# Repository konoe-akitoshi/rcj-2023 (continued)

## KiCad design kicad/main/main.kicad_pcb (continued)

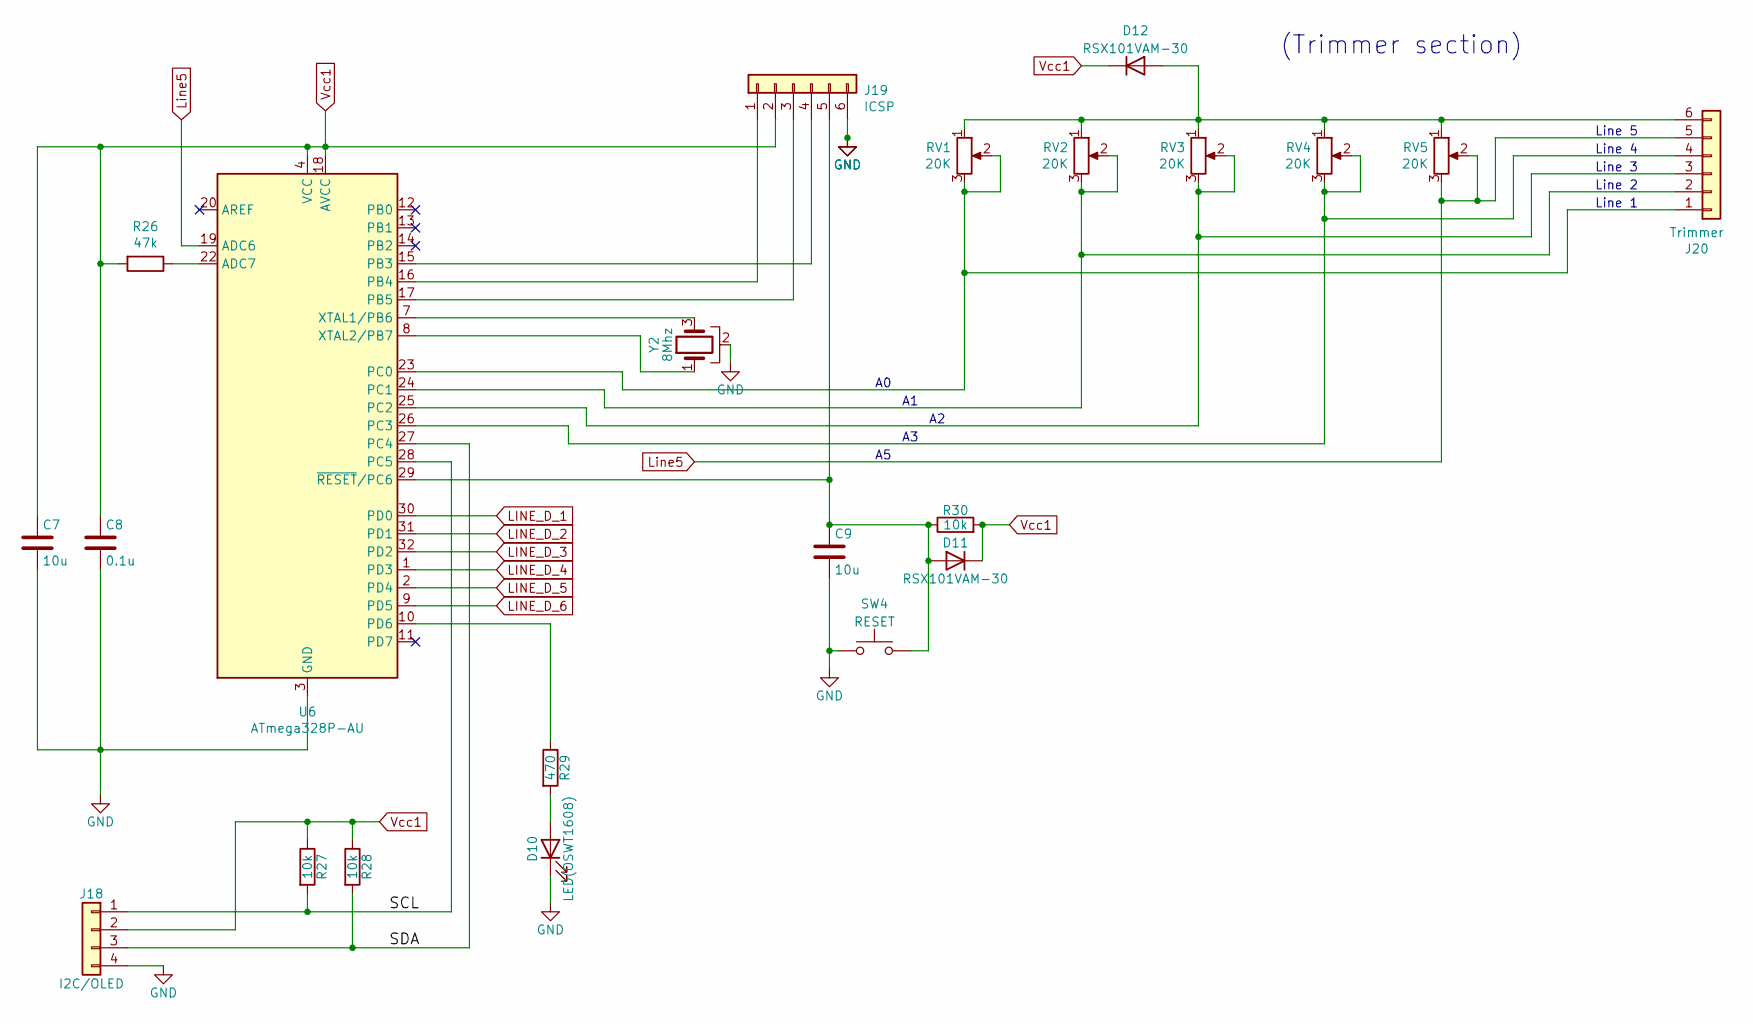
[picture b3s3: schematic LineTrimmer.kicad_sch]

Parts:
C7, C9: 10u; C_0603_1608Metric_Pad1.08x0.95mm_HandSolder
C8: 0.1u; C_0603_1608Metric_Pad1.08x0.95mm_HandSolder
D10: LED(OSWT1608); LED_SMLE13WBC8W1
D11, D12: RSX101VAM-30; D_0805_2012Metric_Pad1.15x1.40mm_HandSolder
J18: I2C/OLED; JSTB4B-ZR
J19: ICSP; JSTB6B-ZR
J20: Trimmer; JSTB6B-ZR
R26: 47k; R_0603_1608Metric_Pad0.98x0.95mm_HandSolder
R27, R28, R30: 10k; R_0603_1608Metric_Pad0.98x0.95mm_HandSolder
R29: 470; R_0603_1608Metric_Pad0.98x0.95mm_HandSolder
RV1, RV2, RV3, RV4, RV5: 20K; Trim-GF063P
SW4: RESET; THAU13-AB-R
U6: ATmega328P-AU; TQFP-32_7x7mm_P0.8mm
Y2: 8Mhz; Resonator-3Pin_W6.0mm_H3.0mm

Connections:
/LineTrimmer/SCL: J18.1, R27.2, U6.28 (PC5)
/LineTrimmer/SDA: J18.3, R28.2, U6.27 (PC4)
LINE_D_1: U6.30 (PD0); also elsewhere on the board
LINE_D_2: U6.31 (PD1); also elsewhere on the board
LINE_D_3: U6.32 (PD2); also elsewhere on the board
LINE_D_4: U6.1 (PD3); also elsewhere on the board
LINE_D_5: U6.2 (PD4); also elsewhere on the board
LINE_D_6: U6.9 (PD5); also elsewhere on the board
Line5: J20.5, RV5.2, RV5.3, U6.19 (ADC6)
unnamed: C9.1, D11.2 (A), J19.5, R30.1, SW4.2, U6.29 (~RESET/PC6)
unnamed: D10.2 (A), R29.2
unnamed: D12.2 (A), J20.6, RV1.1, RV2.1, RV3.1, RV4.1, RV5.1
unnamed: J19.1, U6.16 (PB4)
unnamed: J19.3, U6.17 (PB5)
unnamed: J19.4, U6.15 (PB3)
unnamed: J20.1, RV1.2, RV1.3, U6.23 (PC0)
unnamed: J20.2, RV2.2, RV2.3, U6.24 (PC1)
unnamed: J20.3, RV3.2, RV3.3, U6.25 (PC2)
unnamed: J20.4, RV4.2, RV4.3, U6.26 (PC3)
unnamed: R26.1, U6.22 (ADC7)
unnamed: R29.1, U6.10 (PD6)
unnamed: U6.7 (XTAL1/PB6), Y2.3
unnamed: U6.8 (XTAL2/PB7), Y2.1
SW1_6: C7.2, C8.2, C9.2, D10.1 (K), J18.4, J19.6, SW4.1, U6.3 (GND), U6.5 (GND), U6.21 (GND), Y2.2; also elsewhere on the board
Vcc1: C7.1, C8.1, D11.1 (K), D12.1 (K), J18.2, J19.2, R26.2, R27.1, R28.1, R30.2, U6.4 (VCC), U6.6 (VCC), U6.18 (AVCC)

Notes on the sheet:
Line 1
Line 2
Line 3
(Trimmer section)
Line 4
Line 5

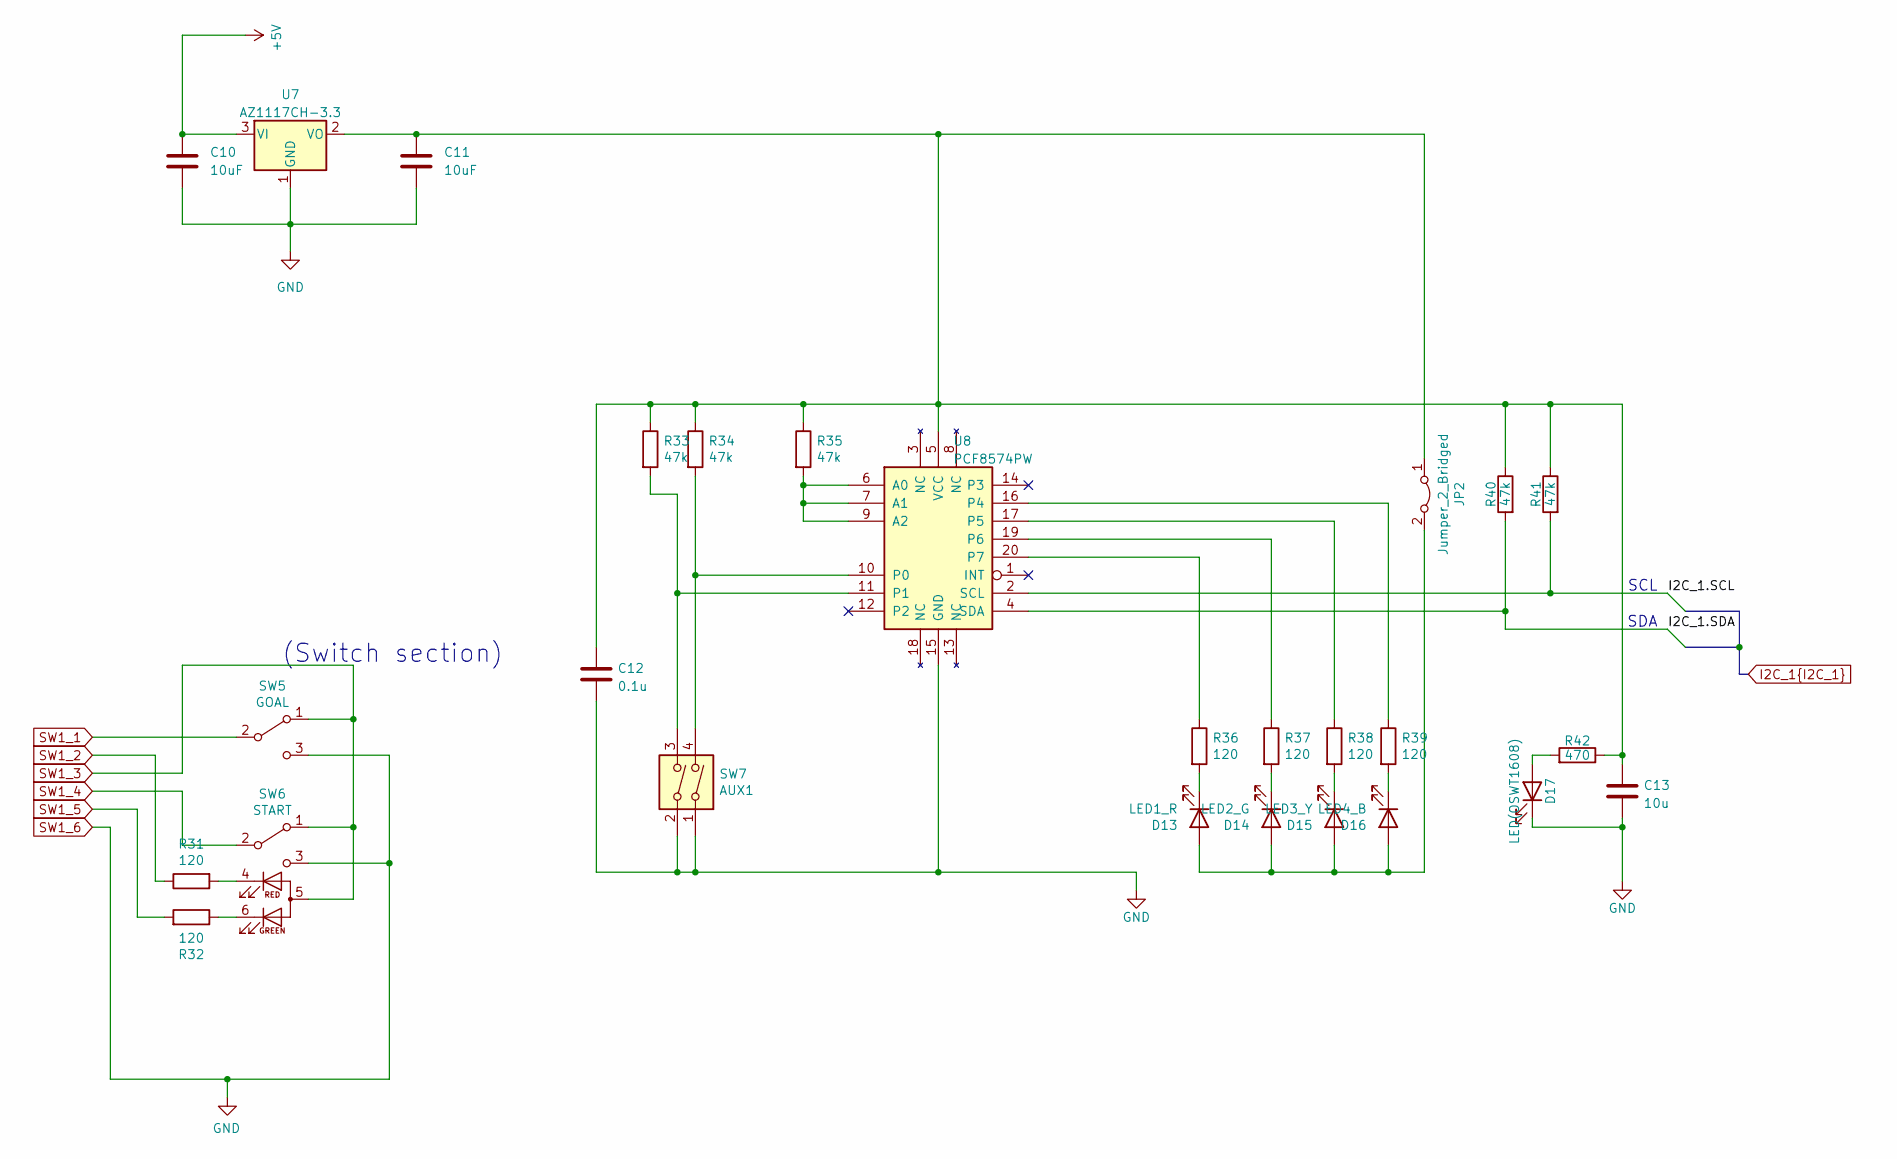
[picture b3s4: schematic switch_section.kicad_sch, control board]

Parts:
C10, C11: 10uF; C_0603_1608Metric_Pad1.08x0.95mm_HandSolder
C12: 0.1u; C_0603_1608Metric_Pad1.08x0.95mm_HandSolder
C13: 10u; C_0603_1608Metric_Pad1.08x0.95mm_HandSolder
D13: LED1_R; LED_SMLE13WBC8W1
D14: LED2_G; LED_SMLE13WBC8W1
D15: LED3_Y; LED_SMLE13WBC8W1
D16: LED4_B; LED_SMLE13WBC8W1
D17: LED(OSWT1608); LED_SMLE13WBC8W1
JP2: Jumper_2_Bridged; PinHeader_1x02_P1.27mm_Vertical
R31, R32, R36, R37, R38, R39: 120; R_0603_1608Metric_Pad0.98x0.95mm_HandSolder
R33, R34, R35, R40, R41: 47k; R_0603_1608Metric_Pad0.98x0.95mm_HandSolder
R42: 470; R_0603_1608Metric_Pad0.98x0.95mm_HandSolder
SW5: GOAL; MFS101D-14-Z
SW6: START; SW_NKK_B-12CCPRM
SW7: AUX1; SW_DIP_SPSTx02_Slide_9.78x7.26mm_W7.62mm_P2.54mm
U7: AZ1117CH-3.3; SOT-223-3_TabPin2
U8: PCF8574PW; TSSOP-20_4.4x6.5mm_P0.65mm

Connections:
+5V: C10.1, U7.3 (VI); also elsewhere on the board
I2C_1.SCL: R41.2, U8.2 (SCL); also elsewhere on the board
I2C_1.SDA: R40.2, U8.4 (SDA); also elsewhere on the board
unnamed: C11.1, C12.1, C13.1, JP2.1 (A), R33.1, R34.1, R35.1, R40.1, R41.1, R42.1, U7.2 (VO), U8.5 (VCC)
unnamed: D13.1 (K), R36.2
unnamed: D13.2 (A), D14.2 (A), D15.2 (A), D16.2 (A), JP2.2 (B)
unnamed: D14.1 (K), R37.2
unnamed: D15.1 (K), R38.2
unnamed: D16.1 (K), R39.2
unnamed: D17.2 (A), R42.2
unnamed: R31.2, SW6.4 (KR)
unnamed: R32.1, SW6.6 (KG)
unnamed: R33.2, SW7.3, U8.11 (P1)
unnamed: R34.2, SW7.4, U8.10 (P0)
unnamed: R35.2, U8.6 (A0), U8.7 (A1), U8.9 (A2)
unnamed: R36.1, U8.20 (P7)
unnamed: R37.1, U8.19 (P6)
unnamed: R38.1, U8.17 (P5)
unnamed: R39.1, U8.16 (P4)
SW1_1: SW5.2 (B); also elsewhere on the board
SW1_2: R31.1; also elsewhere on the board
SW1_3: SW5.1 (A), SW6.1 (A), SW6.5 (A); also elsewhere on the board
SW1_4: SW6.2 (B); also elsewhere on the board
SW1_5: R32.2; also elsewhere on the board
SW1_6: C10.2, C11.2, C12.2, C13.2, D17.1 (K), SW5.3 (C), SW6.3 (C), SW7.1, SW7.2, U7.1 (GND), U8.15 (GND); also elsewhere on the board

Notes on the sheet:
SDA
SCL
(Switch section)

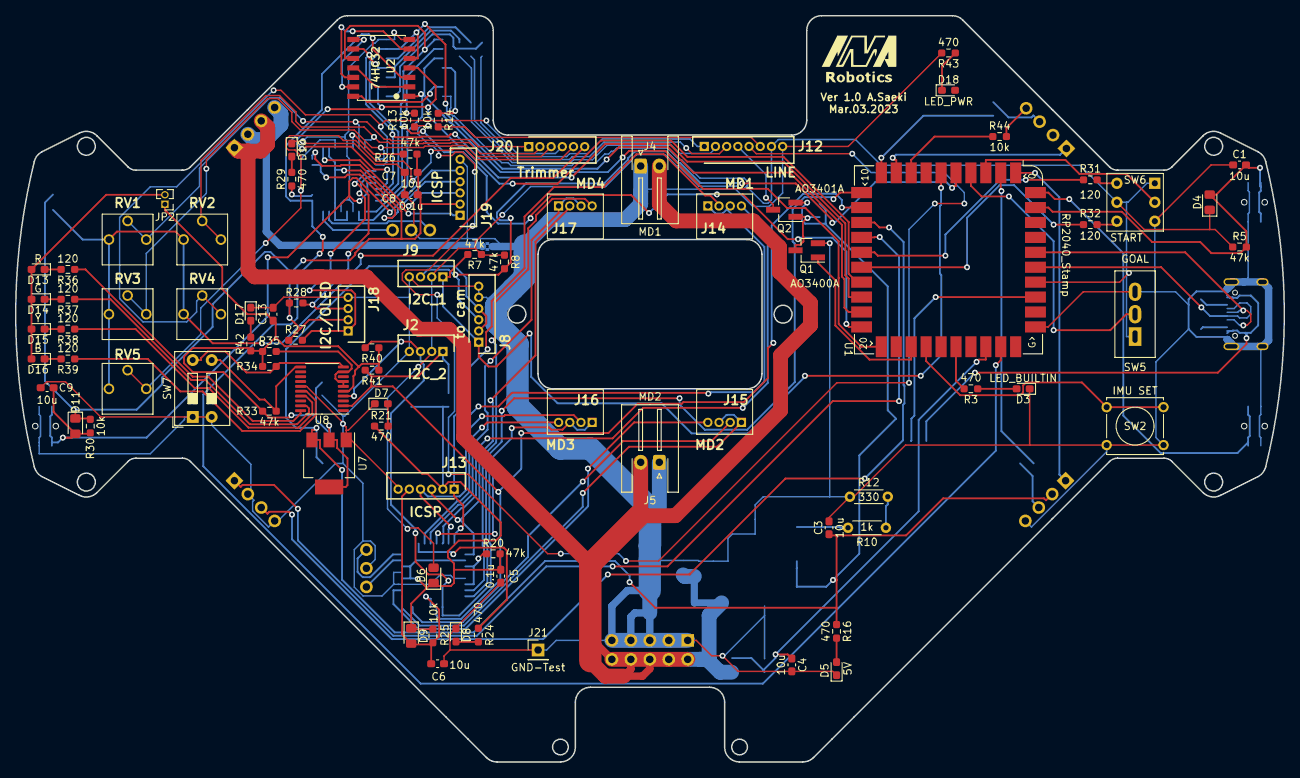
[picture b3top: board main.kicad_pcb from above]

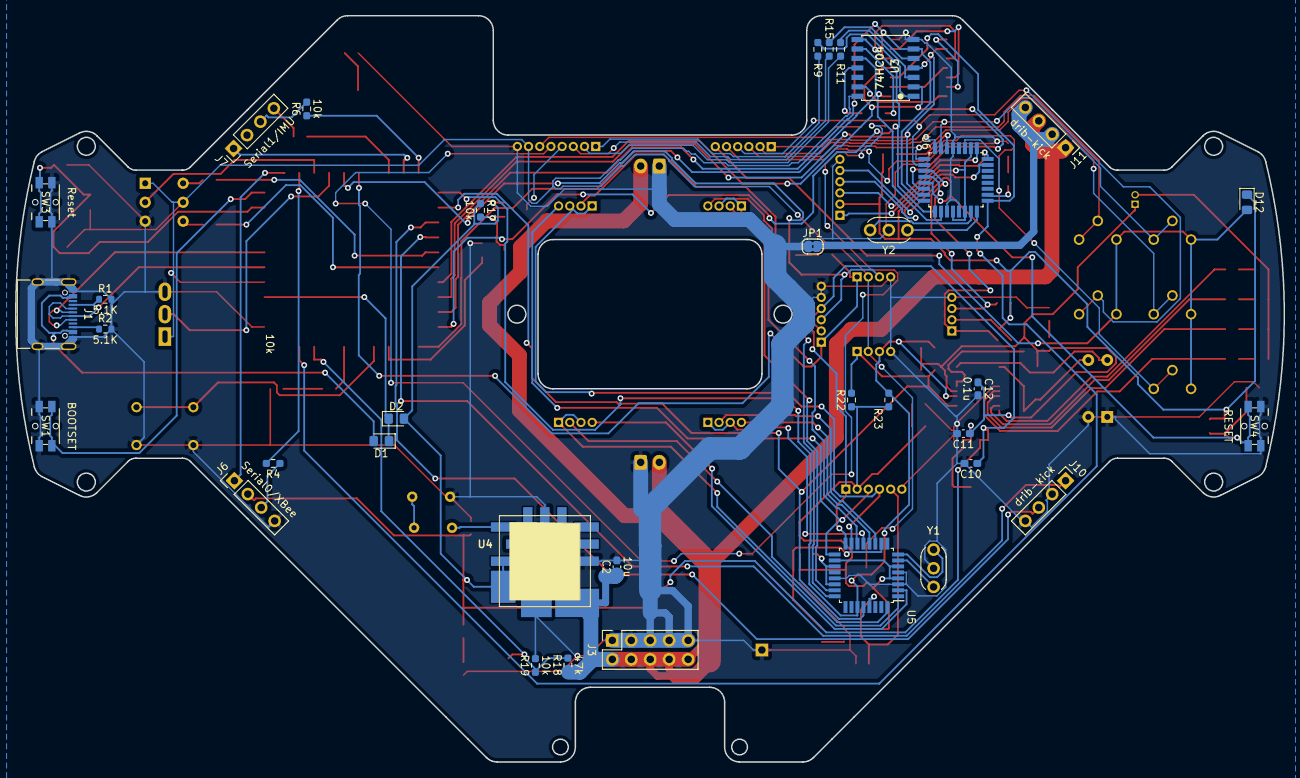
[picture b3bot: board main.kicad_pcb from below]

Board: 2 copper layers, 170.0 x 100.0 mm, 122 parts (35 on the bottom side), 116 nets.

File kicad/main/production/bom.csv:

Designator,Footprint,Quantity,Value,LCSC Part #
C1,0603,1,10u,
C10,0603,1,10uF,
C11,0603,1,10uF,
C12,0603,1,0.1u,
C13,0603,1,10u,
C2,0603,1,10u,
C3,0603,1,10u,
C4,0603,1,10u,
C5,0603,1,0.1u,
C6,0603,1,10u,
C7,0603,1,10u,
C8,0603,1,0.1u,
C9,0603,1,10u,
D1,0805,1,D_Schottky,
"D10, D17",LED_SMLE13WBC8W1,2,LED(OSWT1608),
D11,0805,1,RSX101VAM-30,
D12,0805,1,RSX101VAM-30,
D13,LED_SMLE13WBC8W1,1,R,
D14,LED_SMLE13WBC8W1,1,G,
D15,LED_SMLE13WBC8W1,1,Y,
D16,LED_SMLE13WBC8W1,1,B,
D18,LED_SMLE13WBC8W1,1,LED_PWR,
D2,0805,1,D_Schottky,
D3,LED_SMLE13WBC8W1,1,LED_BUILTIN,
D4,0805,1,RSX101VAM-30TR,
D5,LED_SMLE13WBC8W1,1,5V,
D6,0805,1,RSX101VAM-30TR,
D7,0603,1,LED(OSWT1608),
D8,0603,1,LED(OSWT1608),
D9,0805,1,RSX101VAM-30TR,
J1,USB_C_Receptacle_XKB_U262-16XN-4BVC11,1,USB_C_Receptacle_USB2.0,C319148
"J10, J11",PinHeader_1x04_P2.54mm_Vertical,2,drib-kick,
J12,JSTB8B-ZR,1,LINE,
"J13, J19",JSTB6B-ZR,2,ICSP,
J14,JSTS4B-ZRLFSN,1,MD1,
J15,JSTS4B-ZRLFSN,1,MD2,
J16,JSTS4B-ZRLFSN,1,MD3,
J17,JSTS4B-ZRLFSN,1,MD4,
J18,JSTB4B-ZR,1,I2C/OLED,
J2,JSTB4B-ZR,1,I2C_2,
J20,JSTB6B-ZR,1,Trimmer,
J21,PinHeader_1x01_P2.54mm_Vertical,1,GND-Test,
J3,PinSocket_2x05_P2.54mm_Vertical,1,Power IN,
J4,JST_XH_S2B-XH-A-1_1x02_P2.50mm_Horizontal,1,MD1,
J5,JST_XH_S2B-XH-A-1_1x02_P2.50mm_Horizontal,1,MD2,
J6,PinHeader_1x04_P2.54mm_Vertical,1,Serial0/XBee,
J7,PinHeader_1x04_P2.54mm_Vertical,1,Serial1/IMU,
J8,JSTB6B-ZR,1,to cam,
J9,JSTB4B-ZR,1,I2C_1,
JP1,SolderJumper-2_P1.3mm_Bridged2Bar_RoundedPad1.0x1.5mm,1,Jumper_2_Bridged,
JP2,PinHeader_1x02_P1.27mm_Vertical,1,Jumper_2_Bridged,
Q1,SOT-23_Handsoldering,1,AO3400A,
Q2,SOT-23_Handsoldering,1,AO3401A,
R1,0603,1,5.1K,
R10,R_Axial_DIN0204_L3.6mm_D1.6mm_P5.08mm_Horizontal,1,1k,
R11,0603,1,10k,
R12,R_Axial_DIN0204_L3.6mm_D1.6mm_P5.08mm_Horizontal,1,330,
R13,0603,1,10k,
R14,0603,1,10k,
R15,0603,1,10k,
R16,0603,1,470,
R17,0603,1,10k,
R18,0603,1,47k,
R19,0603,1,10k,
R2,0603,1,5.1K,
R20,0603,1,47k,
R21,0603,1,470,
R22,0603,1,10k,
R23,0603,1,10k,
R24,0603,1,470,
R25,0603,1,10k,
R26,0603,1,47k,
R27,0603,1,10k,
R28,0603,1,10k,
R29,0603,1,470,
R3,0603,1,470,
R30,0603,1,10k,
R31,0603,1,120,
R32,0603,1,120,
R33,0603,1,47k,
R34,0603,1,47k,
R35,0603,1,47k,
R36,0603,1,120,
R37,0603,1,120,
R38,0603,1,120,
R39,0603,1,120,
R4,0603,1,10k,
R40,0603,1,47k,
R41,0603,1,47k,
R42,0603,1,470,
R43,0603,1,470,
R44,0603,1,10k,
R5,0603,1,47k,
R6,0603,1,10k,
R7,0603,1,47k,
R8,0603,1,47k,
R9,0603,1,10k,
"RV1, RV2, RV3, RV4, RV5",Trim-GF063P,5,20K,
SW1,THAU13-AB-R,1,BOOTSET,C318936
SW2,SW_Tactile_Straight_KSA0Axx1LFTR,1,IMU SET,
"SW3, SW4",THAU13-AB-R,2,Reset,
SW5,MFS101D-14-Z,1,GOAL,
SW6,SW_NKK_B-12CCPRM,1,START,
SW7,SW_DIP_SPSTx02_Slide_9.78x7.26mm_W7.62mm_P2.54mm,1,AUX1,
U1,RP2040_Stamp_SMD,1,RP2040_Stamp,
U2,SOP14W,1,74HC32,
U3,SOP14W,1,74HC04,
U4,OKL-T3-W12N-C,1,OKL-T_3-W12N-C,
"U5, U6",TQFP-32_7x7mm_P0.8mm,2,ATmega328P-AU,
U7,SOT-223-3_TabPin2,1,AZ1117CH-3.3,
U8,TSSOP-20_4.4x6.5mm_P0.65mm,1,PCF8574PW,
"Y1, Y2",Resonator-3Pin_W6.0mm_H3.0mm,2,8Mhz,

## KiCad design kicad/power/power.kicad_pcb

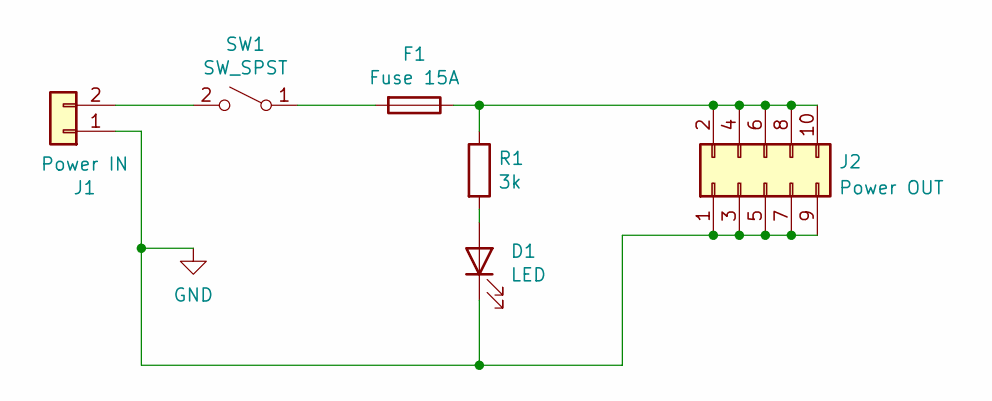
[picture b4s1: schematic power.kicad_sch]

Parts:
D1: LED; LED_SMLE13WBC8W1
F1: Fuse 15A; FUSE_35222
J1: Power IN; AMASS_XT60-M_1x02_P7.20mm_Vertical
J2: Power OUT; PinHeader_2x05_P2.54mm_Vertical
R1: 3k; R_0603_1608Metric_Pad0.98x0.95mm_HandSolder
SW1: SW_SPST; SW_SPST_POWER

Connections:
GND: D1.1 (K), J1.1, J2.1, J2.3, J2.5, J2.7, J2.9
unnamed: D1.2 (A), R1.2
unnamed: F1.1, J2.2, J2.4, J2.6, J2.8, J2.10, R1.1
unnamed: F1.2, SW1.1 (A)
unnamed: J1.2, SW1.2 (B)

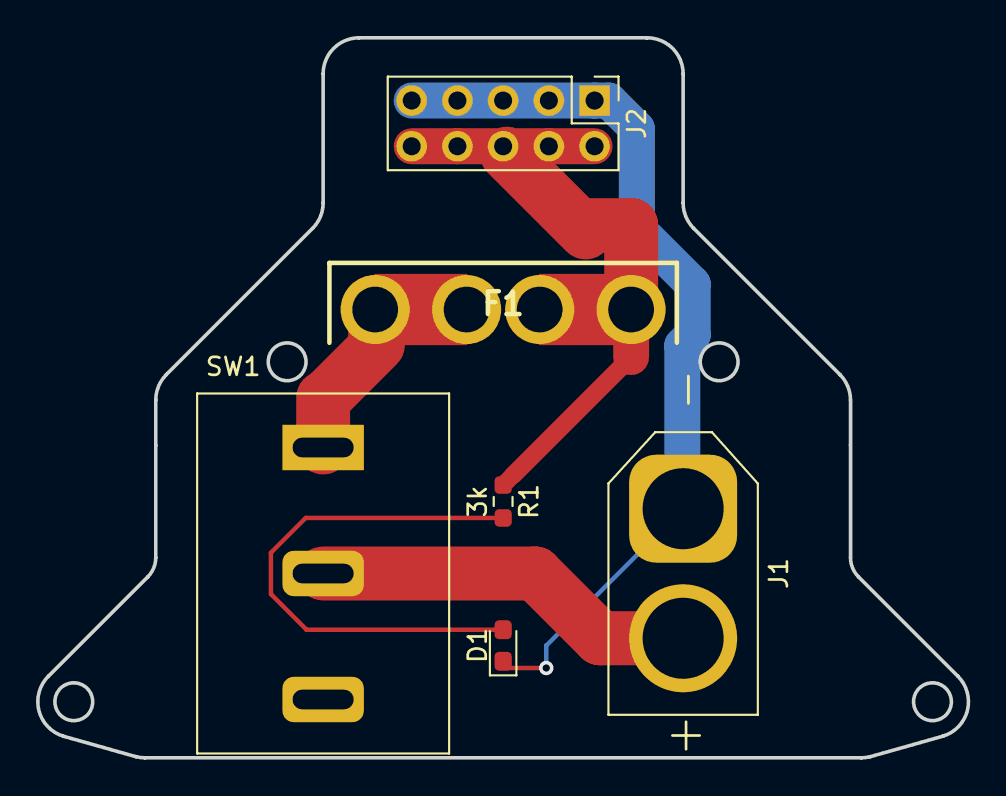
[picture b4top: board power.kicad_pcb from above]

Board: 2 copper layers, 51.7 x 40.0 mm, 6 parts (0 on the bottom side), 5 nets.

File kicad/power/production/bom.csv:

Designator,Footprint,Quantity,Value,LCSC Part #
D1,LED_SMLE13WBC8W1,1,LED,
F1,FUSE_35222,1,Fuse 15A,
J1,AMASS_XT60-M_1x02_P7.20mm_Vertical,1,Power IN,
J2,PinHeader_2x05_P2.54mm_Vertical,1,Power OUT,
R1,0603,1,3k,
SW1,SW_SPST_POWER,1,SW_SPST,

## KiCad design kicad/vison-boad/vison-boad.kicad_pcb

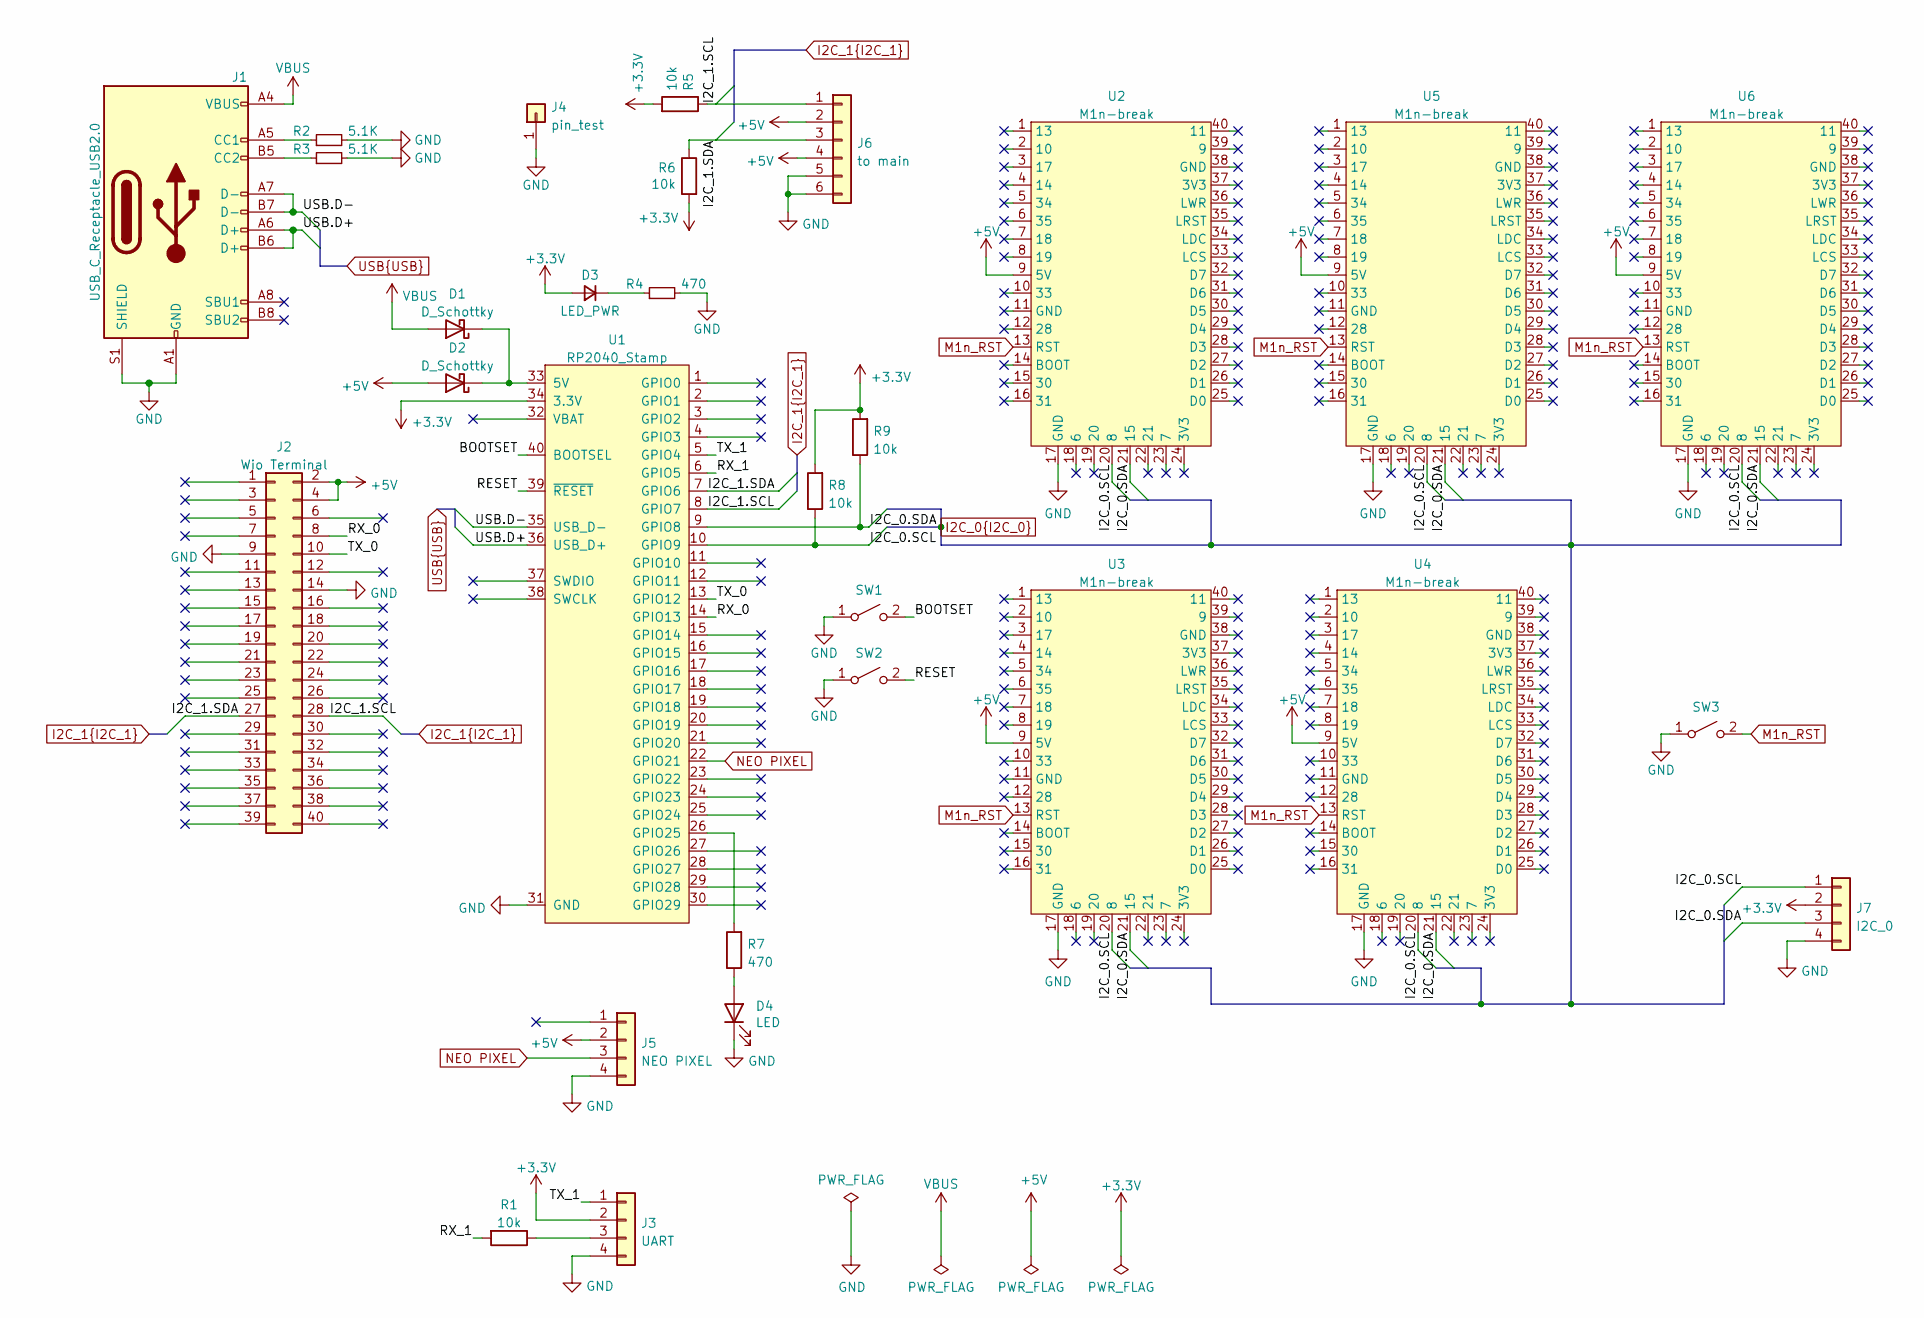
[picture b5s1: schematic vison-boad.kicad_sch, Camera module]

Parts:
D1, D2: D_Schottky; D_0805_2012Metric_Pad1.15x1.40mm_HandSolder
D3: LED_PWR; LED_SMLE13WBC8W1
D4: LED; LED_SMLE13WBC8W1
J1: USB_C_Receptacle_USB2.0; USB_C_Receptacle_XKB_U262-16XN-4BVC11; LCSC C319148
J2: Wio Terminal; PinHeader_2x20_P2.54mm_Vertical_SMD
J3: UART; JSTB4B-ZR
J4: pin_test; Pin_D0.7mm_L6.5mm_W1.8mm_FlatFork
J5: NEO PIXEL; JSTB4B-ZR
J6: to main; JSTB6B-ZR
J7: I2C_0; JSTB4B-ZR
R1, R5, R6, R8, R9: 10k; R_0603_1608Metric_Pad0.98x0.95mm_HandSolder
R2, R3: 5.1K; R_0603_1608Metric_Pad0.98x0.95mm_HandSolder
R4, R7: 470; R_0603_1608Metric_Pad0.98x0.95mm_HandSolder
SW1: BOOTSET; Panasonic_EVQPUJ_EVQPUA; LCSC C318936
SW2: RESET; Panasonic_EVQPUJ_EVQPUA; LCSC C318936
SW3: M1n_RST; Panasonic_EVQPUJ_EVQPUA; LCSC C318936
U1: RP2040_Stamp; RP2040_Stamp_SMD
U2, U3, U4, U5, U6: M1n-break

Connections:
+3.3V: D3.2 (A), J3.2, J7.2, R5.2, R6.2, R8.2, R9.2, U1.34 (3.3V)
+5V: D2.2 (A), J2.2, J2.4, J5.2, J6.2, J6.4, U2.9 (5V), U3.9 (5V), U4.9 (5V), U5.9 (5V), U6.9 (5V)
/BOOTSET: SW1.2 (B), U1.40 (BOOTSEL)
/RESET: SW2.2 (B), U1.39 (~RESET)
/RX_0: J2.8, U1.14 (GPIO13)
/RX_1: R1.2, U1.6 (GPIO5)
/TX_0: J2.10, U1.13 (GPIO12)
/TX_1: J3.1, U1.5 (GPIO4)
GND: D4.1 (K), J1.A1 (GND), J1.A12 (GND), J1.B1 (GND), J1.B12 (GND), J1.S1 (SHIELD), J2.9, J2.14, J3.4, J4.1, J5.4, J6.5, J6.6, J7.4, R2.2, R3.2, R4.2, SW1.1 (A), SW2.1 (A), SW3.1 (A), U1.31 (GND), U2.17 (GND), U3.17 (GND), U4.17 (GND), U5.17 (GND), U6.17 (GND)
I2C_0.SCL: J7.1, R8.1, U1.10 (GPIO9), U2.20 (8), U3.20 (8), U4.20 (8), U5.20 (8), U6.20 (8)
I2C_0.SDA: J7.3, R9.1, U1.9 (GPIO8), U2.21 (15), U3.21 (15), U4.21 (15), U5.21 (15), U6.21 (15)
I2C_1.SCL: J2.28, J6.1, R5.1, U1.8 (GPIO7)
I2C_1.SDA: J2.27, J6.3, R6.1, U1.7 (GPIO6)
M1n_RST: SW3.2 (B), U2.13 (RST), U3.13 (RST), U4.13 (RST), U5.13 (RST), U6.13 (RST)
NEO PIXEL: J5.3, U1.22 (GPIO21)
unnamed: D1.1 (K), D2.1 (K), U1.33 (5V)
unnamed: D3.1 (K), R4.1
unnamed: D4.2 (A), R7.1
unnamed: J1.A5 (CC1), R2.1
unnamed: J1.B5 (CC2), R3.1
unnamed: J3.3, R1.1
unnamed: R7.2, U1.26 (GPIO25)
USB.D+: J1.A6 (D+), J1.B6 (D+), U1.36 (USB_D+)
USB.D-: J1.A7 (D-), J1.B7 (D-), U1.35 (USB_D-)
VBUS: D1.2 (A), J1.A4 (VBUS), J1.A9 (VBUS), J1.B4 (VBUS), J1.B9 (VBUS)

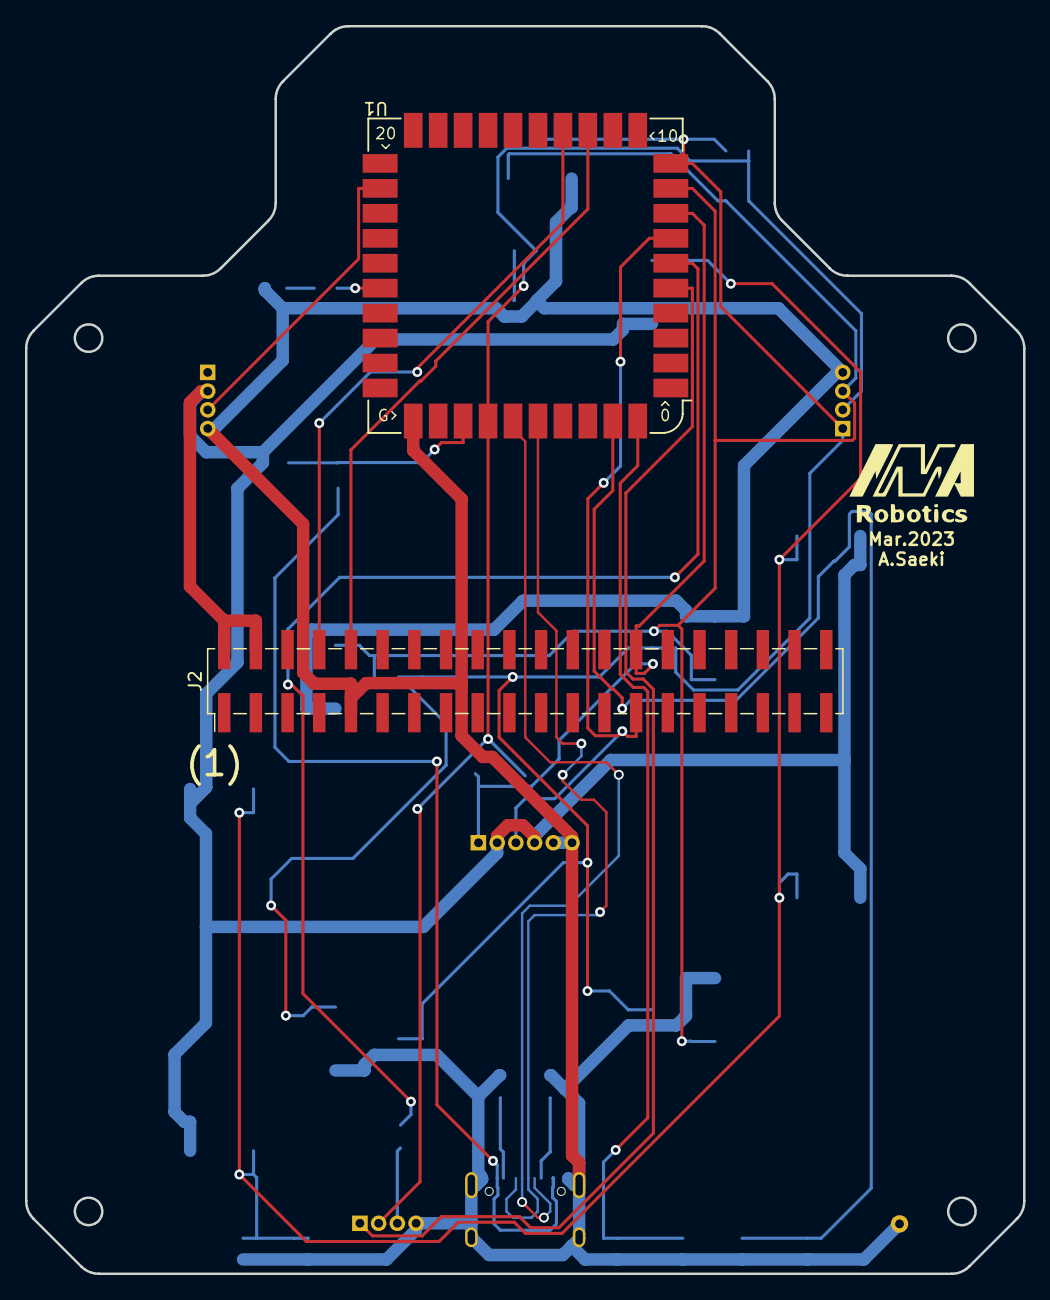
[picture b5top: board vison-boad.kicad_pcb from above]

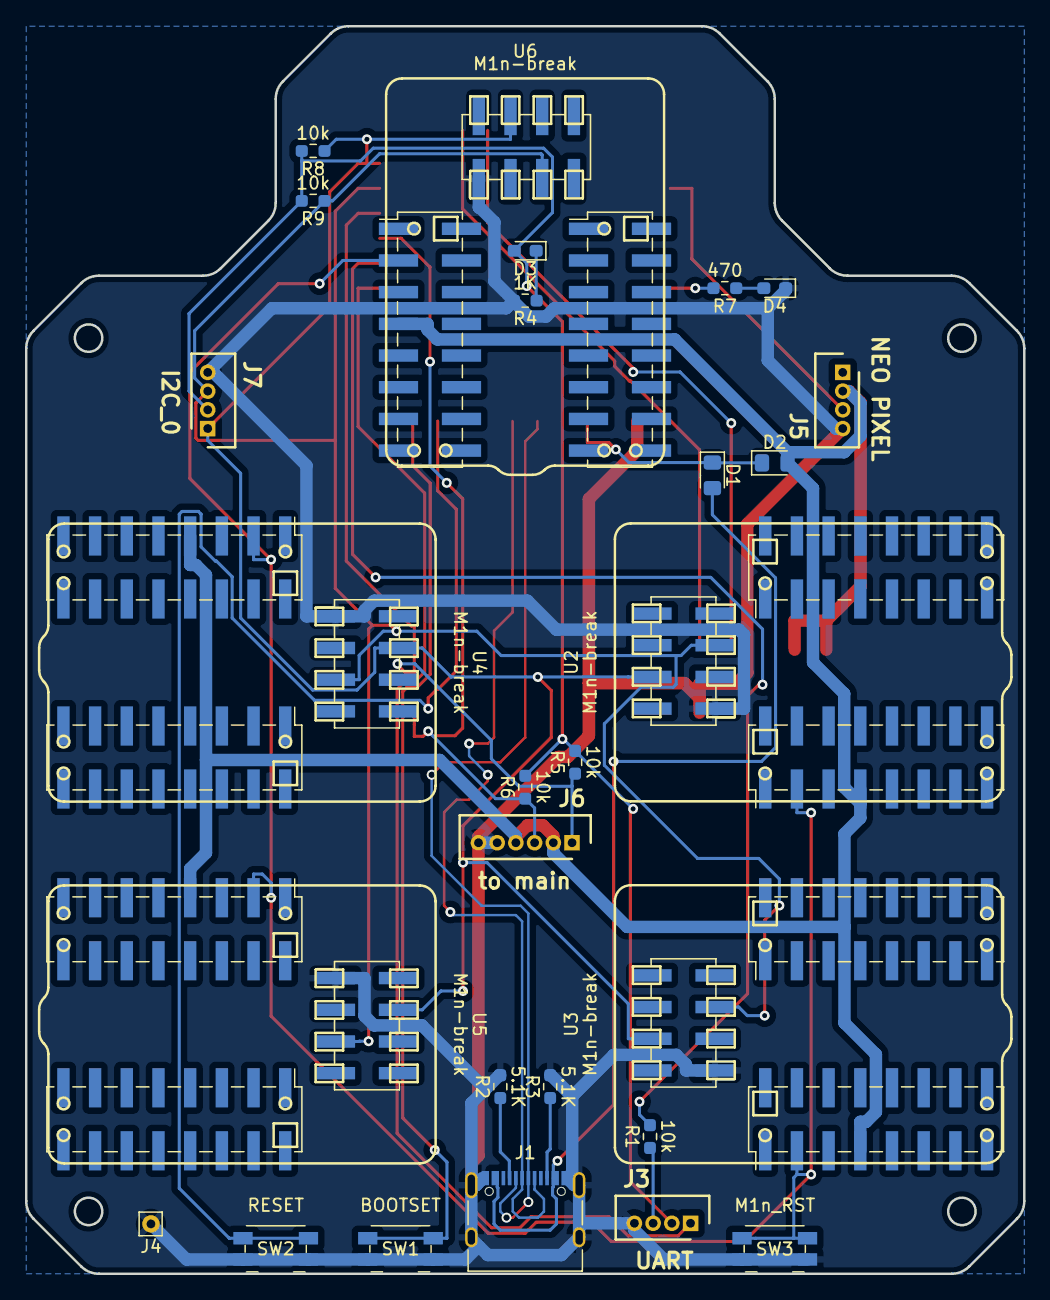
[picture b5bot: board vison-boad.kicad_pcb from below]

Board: 2 copper layers, 80.0 x 100.0 mm, 29 parts (27 on the bottom side), 25 nets.

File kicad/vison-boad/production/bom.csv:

Designator,Footprint,Quantity,Value,LCSC Part #
D1,0805,1,D_Schottky,
D2,0805,1,D_Schottky,
D3,LED_SMLE13WBC8W1,1,LED_PWR,
D4,LED_SMLE13WBC8W1,1,LED,
J1,USB_C_Receptacle_XKB_U262-16XN-4BVC11,1,USB_C_Receptacle_USB2.0,C319148
J2,PinHeader_2x20_P2.54mm_Vertical_SMD,1,Wio Terminal,
J3,JSTB4B-ZR,1,UART,
J4,Pin_D0.7mm_L6.5mm_W1.8mm_FlatFork,1,pin_test,
J5,JSTB4B-ZR,1,NEO PIXEL,
J6,JSTB6B-ZR,1,to main,
J7,JSTB4B-ZR,1,I2C_0,
R1,0603,1,10k,
R2,0603,1,5.1K,
R3,0603,1,5.1K,
R4,0603,1,1K,
R5,0603,1,10k,
R6,0603,1,10k,
R7,0603,1,470,
R8,0603,1,10k,
R9,0603,1,10k,
SW1,Panasonic_EVQPUJ_EVQPUA,1,BOOTSET,C318936
SW2,Panasonic_EVQPUJ_EVQPUA,1,RESET,C318936
SW3,Panasonic_EVQPUJ_EVQPUA,1,M1n_RST,C318936
U1,RP2040_Stamp_SMD,1,RP2040_Stamp,
"U2, U3, U4, U5, U6",M1n-break,5,M1n-break,

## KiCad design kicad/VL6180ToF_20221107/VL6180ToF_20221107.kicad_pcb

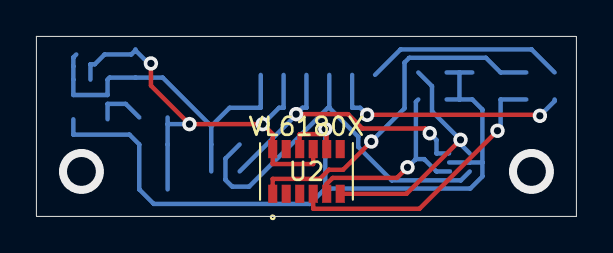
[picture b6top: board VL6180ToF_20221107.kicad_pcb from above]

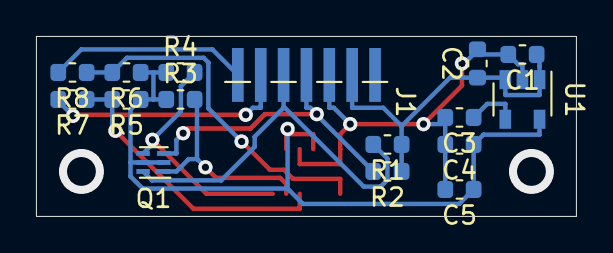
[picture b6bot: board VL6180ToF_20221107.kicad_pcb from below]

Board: 2 copper layers, 30.0 x 10.0 mm, 17 parts (16 on the bottom side), 12 nets.

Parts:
C1, C4: 1u; C_0603_1608Metric
C2, C5: 0.1u; C_0603_1608Metric
C3: 0.01u; C_0603_1608Metric
J1: Conn_01x07; Pin_1x07_P1.27mm_SMD
Q1: SSM6N42FE; WSON-6_1.5x1.5mm_P0.5mm
R1, R2, R3, R4: 10k; R_0603_1608Metric
R5, R6: 47k; R_0603_1608Metric
R7, R8: 1k; R_0603_1608Metric
U1: Si91841; SOT-23-5
U2: VL6180X; VL6180XV0NR&slash_1

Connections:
GND: C1.2, C2.2, C3.2, C4.2, C5.2, J1.3, U1.2 (GND), U2.9 (AVSS_VCSEL), U2.12 (AVSS)
unnamed: C3.1, U1.4 (NR)
unnamed: J1.4, Q1.3 (D), R2.2
unnamed: J1.5, Q1.6 (D), R1.2
unnamed: J1.6, R7.2
unnamed: J1.7, R8.2
unnamed: Q1.1 (S), R3.2, U2.5 (SCL)
unnamed: Q1.4 (S), R4.2, U2.6 (SDA)
unnamed: R5.2, R7.1, U2.4 (GPIO0)
unnamed: R6.2, R8.1, U2.1 (GPIO1)
VCC: C1.1, C2.1, J1.2, R1.1, R2.1, U1.1 (IN), U1.3 (EN)
VDD: C4.1, C5.1, Q1.2 (G), Q1.5 (G), R3.1, R4.1, R5.1, R6.1, U1.5 (OUT), U2.8 (AVDD_VCSEL), U2.10 (AVDD)

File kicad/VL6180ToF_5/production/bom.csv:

Designator,Footprint,Quantity,Value,LCSC Part #
C1,0603,1,1u,
C2,0603,1,0.1u,
C3,0603,1,0.01u,
C4,0603,1,1u,
C5,0603,1,0.1u,
J1,Pin_1x07_P1.27mm_SMD,1,Conn_01x07,
Q1,WSON-6_1.5x1.5mm_P0.5mm,1,SSM6N42FE,
R1,0603,1,10k,
R2,0603,1,10k,
R3,0603,1,10k,
R4,0603,1,10k,
R5,0603,1,47k,
R6,0603,1,47k,
R7,0603,1,1k,
R8,0603,1,1k,
U1,SOT-23-5,1,Si91841,
U2,VL6180XV0NR&slash_1,1,VL6180X,
